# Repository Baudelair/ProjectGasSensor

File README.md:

# ProjectGasSensor

Durant les différents travaux pratiques que nous avons eu, nous avons pu créer un capteur de gaz connecté. Nous avons tout d'abord réalisé un capteur de gaz depuis le début dans une salle blanche pour ensuite la connecté à une board Arduino. Dans ce repository, vous pourrez avoir accés au datasheet du capteur de gaz mais aussi le PCB conçu pour être un shield Arduino Uno.
Ainsi, on se retrouve avec un détecteur de fumée connecté à LoRa et qui a la capacité de sonné en cas de détection de fumée.

## Partie Kicad 

### Conception du traitement du signal du capteur de gaz

Nous avons utilisé un montage suggéré par Monsieur Noullet (https://noullet-gei.gitlab.io/iss_analog/) dont le but du filtre passe-bande est d'extraire toute l'information utile du capteur et atténuer la composante de bruit.
Vous pouvez voir ci-dessous le schéma électrique de ce filtrage ainsi que des autres composants utilisés sur le shield.

### Réalisation du shield Arduino Uno

Dans la partie que nous avons désiré réaliser, nous avons décidé de créer un shield avec comme composant notre capteur de gaz avec toute sa partie traîtement du signal ainsi qu'un buzzer et d'une LED. Tout ce système est relié à un programme Arduino décrit ci-dessous. Nous avons aussi souhaité rajouter un module LoRa qui permet de se connecter à l'interface IoT "The Things Network". On se retrouve ainsi avec ce shield (sous View3D de Kicad) :

On peut distinguer sur la partie haute à droite, le traitements du signal avec J1 le capteur de gaz. U1 correspond au connecteur pour le module LoRa et J2 correspond à une connectique pour le capteur de gaz de type Groove.

## Partie code 

Dans un premier temps, pour le bon fonctionnement de tous les composants, une étape de calibration est nécessaire. Pour communiquer avec le réseau The Thing Network, il faut entrer des valeurs de clé comme la devAddr (adresse de notre réseau), nwkSKey (clé pour notre réseau) et appSKey (clé de l'application de notre réseau). Pour le capteur de gaz, on doit configurer R0 afin de calibrer le capteur à l'atmosphère ambiante et ainsi détecter la présence d'un gaz après.
Ensuite, viens l'étape où l'on récupére les données du capteur de gaz et on les envoie grâce à LoRa sur notre réseau. Par la suite, il est possible d'utiliser ces informations comme bon nous semble. 

## Elargissement

Pour améliorer notre projet, il est possible de faire une application Androïd qui pourrait avertir l'utilisateur de la présence du fumée au sein de sa maison. Si jamais il n'y pas de réponse de sa part, les pompiers pourraient être averti pour éviter tout risque. 
Cette architecture peut aussi être utilisé dans différents domaines comme la détection de place de parking, le détecteur de présence... Il suffit juste de changer le capteur de gaz par un autre (ainsi que modifier la partie traitement du signal).

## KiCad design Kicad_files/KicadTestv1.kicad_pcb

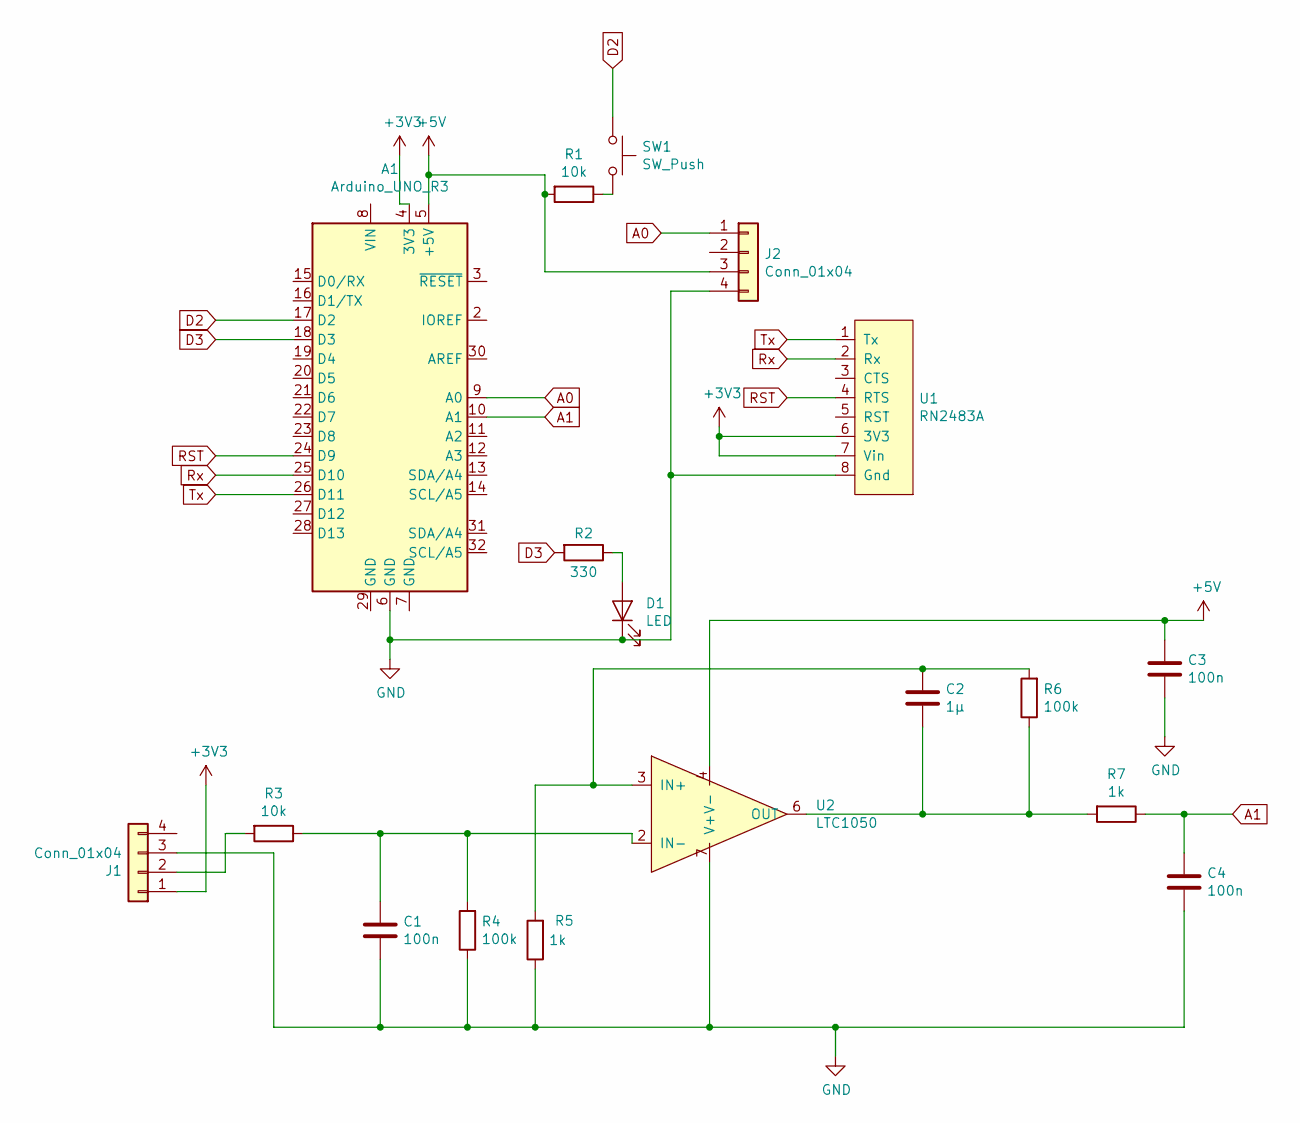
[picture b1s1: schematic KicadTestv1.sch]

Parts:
A1: Arduino_UNO_R3
C1, C3, C4: 100n; C_Axial_L3.8mm_D2.6mm_P7.50mm_Horizontal
C2: 1µ; C_Rect_L7.0mm_W4.5mm_P5.00mm
D1: LED; LED_D3.0mm
J1: Conn_01x04; TO-5-4_1
J2: Conn_01x04; PinHeader_1x04_P2.00mm_Vertical
R1, R3: 10k; R_Axial_DIN0204_L3.6mm_D1.6mm_P7.62mm_Horizontal
R2: 330; R_Axial_DIN0204_L3.6mm_D1.6mm_P7.62mm_Horizontal
R4, R6: 100k; R_Axial_DIN0204_L3.6mm_D1.6mm_P7.62mm_Horizontal
R5, R7: 1k; R_Axial_DIN0204_L3.6mm_D1.6mm_P7.62mm_Horizontal
SW1: SW_Push; SW_PUSH_6mm
U1: RN2483A; Socket_Strip_Arduino_1x08
U2: LTC1050; DIP-8_W7.62mm_LongPads

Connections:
+3V3: A1.4 (3V3), J1.1, U1.6 (3V3), U1.7 (Vin)
+5V: A1.5 (+5V), C3.1, J2.3, R1.2, U2.4 (V-)
A0: A1.9 (A0), J2.1
A1: A1.10 (A1), C4.1, R7.1
D2: A1.17 (D2), SW1.1
D3: A1.18 (D3), R2.2
GND: A1.6 (GND), C1.2, C3.2, C4.2, D1.1 (K), J1.3, J2.4, R4.1, R5.1, U1.8 (Gnd), U2.7 (V+)
unnamed: C1.1, R3.1, R4.2, U2.2 (IN-)
unnamed: C2.1, R5.2, R6.2, U2.3 (IN+)
unnamed: C2.2, R6.1, R7.2, U2.6 (OUT)
unnamed: D1.2 (A), R2.1
unnamed: J1.2, R3.2
unnamed: R1.1, SW1.2
RST: A1.24 (D9), U1.4 (RTS)
Rx: A1.25 (D10), U1.2 (Rx)
Tx: A1.26 (D11), U1.1 (Tx)

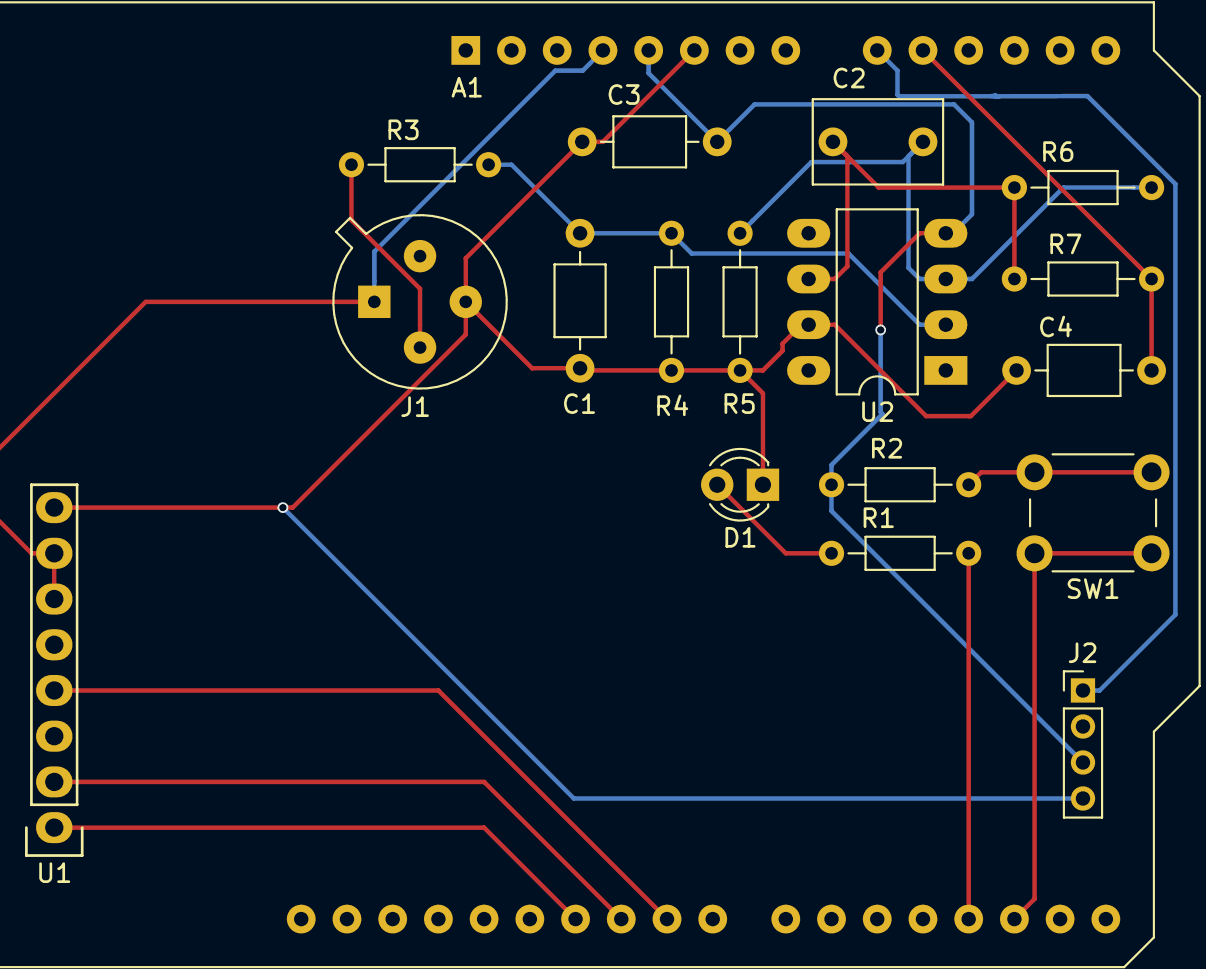
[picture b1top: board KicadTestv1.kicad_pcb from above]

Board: 2 copper layers, 18 parts (0 on the bottom side), 16 nets.

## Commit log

2019-11-15 creation
2019-11-18 Library
2019-11-18 gasSensor+LoRa OK
2019-11-25 Mise en place Kicad
2019-12-03 clean arduino sketchs
2019-12-03 moved kicad files
2019-12-04 Ajout Lib pour RN2483 & Modificition Empreinte et cablage
2019-12-11 Modification empreinte et ajout circuit capteur AIME + faire routage
2019-12-11 Debut cablages
2019-12-13 Cablage fait + verifier prochain commit si le module LoRa rentre
2020-01-06 Mise en beauté de Kicad
2020-01-06 Modification Readme.md
2020-01-07 Ajout de README + dossier pour image du README
2020-01-07 Modif Readme
